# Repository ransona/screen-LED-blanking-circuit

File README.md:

This is a circuit to modify standard monitor to only turn on LED during 2-photon microscope scan line turn around. It includes knobs to tune onset time relative to end of acquisition of line signal, and on time length. It was designed and built by Eric D'Andria.

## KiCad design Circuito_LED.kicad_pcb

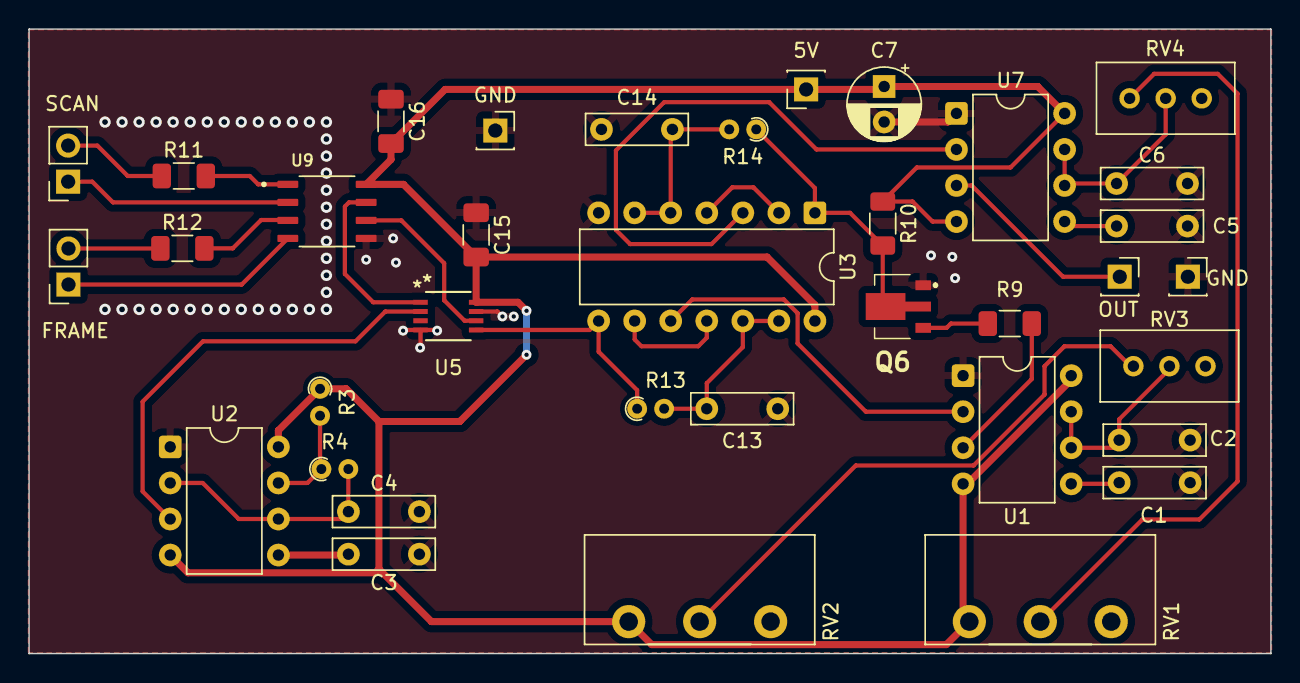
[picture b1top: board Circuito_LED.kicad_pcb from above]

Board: 2 copper layers, 87.5 x 44.0 mm, 36 parts (0 on the bottom side), 31 nets.

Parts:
5V: +5V; PinSocket_1x01_P2.54mm_Vertical
C1, C3, C4, C5: 10n; C_Rect_L7.0mm_W2.0mm_P5.00mm
C2, C6: 500p; C_Rect_L7.0mm_W2.0mm_P5.00mm
C7: 4.7u; CP_Radial_D5.0mm_P2.50mm
C13, C14: 25p; C_Rect_L7.0mm_W2.0mm_P5.00mm
C15, C16: 47n; C_1206_3216Metric_Pad1.33x1.80mm_HandSolder
FRAME: SCAN; PinSocket_1x02_P2.54mm_Vertical
GND: OUT; PinSocket_1x01_P2.54mm_Vertical
GND#2: GND; PinSocket_1x01_P2.54mm_Vertical
OUT: OUT; PinSocket_1x01_P2.54mm_Vertical
Q6: BSS87,115; BSS87115
R3: 8k; R_Axial_DIN0204_L3.6mm_D1.6mm_P1.90mm_Vertical
R4: 470; R_Axial_DIN0204_L3.6mm_D1.6mm_P1.90mm_Vertical
R9: 100; R_1206_3216Metric_Pad1.30x1.75mm_HandSolder
R10: 1k; R_1206_3216Metric_Pad1.30x1.75mm_HandSolder
R11, R12: 470; R_1206_3216Metric_Pad1.30x1.75mm_HandSolder
R13, R14: 680; R_Axial_DIN0204_L3.6mm_D1.6mm_P1.90mm_Vertical
RV1, RV2: 10k; Potentiometer_Piher_T-16H_Single_Horizontal
RV3, RV4: 10k; Potentiometer_Bourns_3296W_Vertical
SCAN: LED; PinSocket_1x02_P2.54mm_Vertical
U1, U2, U7: TLC555xP; DIP-8_W7.62mm
U3: 4011; DIP-14_W7.62mm
U5: 74LVC2G157; DCT8
U9: IL611-3E; NVE_IL611-3E

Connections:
+5V: 5V.1, C7.1, C15.2, C16.2, R3.1, R10.1, RV1.1, RV2.1, U1.4 (R), U1.8 (VCC), U2.4 (R), U2.8 (VCC), U3.14 (VDD), U5.8 (VCC), U7.4 (R), U7.8 (VCC), U9.8 (VDD)
/LED+: R11.1, SCAN.2 (Ext)
/LED-: SCAN.1 (In), U9.2 (IN1-)
/SCAN+: FRAME.2 (Ext), R12.1
/SCAN-: FRAME.1 (In), U9.4 (IN2-)
DELAY: R9.1, U1.3 (Q)
GND: C1.1, C2.2, C3.1, C4.2, C5.1, C6.2, C7.2, C13.1, C14.1, C15.1, C16.1, GND.1, GND#2.1, Q6.1 (S), U1.1 (GND), U2.1 (GND), U3.7 (VSS), U5.4 (GND), U5.7 (~G), U7.1 (GND), U9.5 (GND)
LED_ON: U5.1 (A), U9.7 (OUT1)
LO: U2.3 (Q), U5.2 (B)
MONO: OUT.1, U7.3 (Q)
NDELAY: Q6.2 (D_1), Q6.4 (D_2), R10.2, R14.1, U3.1
unnamed: C13.2, R13.2, U3.12, U3.13
unnamed: C14.2, R14.2, U3.5, U3.6
unnamed: Q6.3 (G), R9.2
unnamed: RV1.2, RV4.1
unnamed: RV2.2, RV3.1
unnamed: C1.2, U1.5 (CV)
unnamed: C2.1, RV3.2, U1.6 (THR), U1.7 (DIS)
unnamed: U1.2 (TR), U3.10
unnamed: C3.2, U2.5 (CV)
unnamed: R3.2, R4.1, U2.7 (DIS)
unnamed: C4.1, R4.2, U2.2 (TR), U2.6 (THR)
unnamed: U3.2, U3.4
unnamed: U3.9, U3.11
unnamed: R13.1, U3.8, U5.5 (Y)
unnamed: C5.2, U7.5 (CV)
unnamed: C6.1, RV4.2, U7.6 (THR), U7.7 (DIS)
unnamed: U3.3, U7.2 (TR)
unnamed: R11.2, U9.1 (IN1+)
unnamed: R12.2, U9.3 (IN2+)
SCAN: U5.6 (~A/B), U9.6 (OUT2)
